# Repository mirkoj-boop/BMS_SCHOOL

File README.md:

# BMS  4S Li-Ion Battery Management System

> BMS PCB designed in KiCad for a 4S Li-Ion battery pack integrates cell protection, passive balancing, isolated AC/DC charging, and LED battery indication on a single board.

---

## Features

- **4S Li-Ion protection** via BQ77905 - OVP, UVP, OCD, SCD, OT/UT per cell
- **Passive cell balancing** (VC1–VC5)
- **Isolated flyback AC/DC charger** - VIPer26LD + PC817 + TL431 feedback
- **10-segment LED battery indicator** - LM3914
- **AC EMI filter** - X+Y capacitors, varistor surge protection
- **Temperature monitoring** - NTC thermistor on TS pin

---

## Specifications

| Parameter | Value |
|---|---|
| Cell configuration | 4S Li-Ion |
| Nominal pack voltage | 14.4 V |
| Full charge voltage | 16.8 V |
| Charge current | 2 A |
| Charger input |230V(50Hz) |
| Design tool | KiCad 10 |

---

## Key Components

| Reference | Part | Function |
|---|---|---|
| U21 | BQ77905 | BMS IC - protection + balancing |
| U18 | VIPer26LD | Flyback AC/DC controller |
| U3 | LM3914 | LED battery level indicator |
| U2 | PC817 | Optocoupler - galvanic isolation |
| U1 | TL431DBZ | Voltage reference - feedback |
| T3 | Würth EE20_10_6_750811647 | Flyback transformer |
| Q22, Q23 | CSD19531Q5A | N-ch MOSFETs - charge/discharge path |
| D2 | KBPC | AC bridge rectifier |
| FL2 | P300PL104M275xC332 | AC EMI filter |
| RV01 | Varistor | Surge/overvoltage protection |
| TH2 | Thermistor | Temperature sense (TS pin) |

---

## System Architecture

```
230V(50Hz) ──► FL2 (EMI filter) ──► D2 (rectifier) ──► U18 VIPer26LD
                                                              │
                                                         T3 transformer
                                                        ╱             ╲
                                               Aux winding         Secondary
                                                    │                   │
                                               VDD (~5V)           VO (16.8V)
                                                                        │
                                                              PC817 + TL431
                                                             (isolated feedback)

4S Pack (BT15–BT18) ──► BQ77905 ──► CSD19531Q5A MOSFETs ──► PACK+ / PACK-
                              │
                          LM3914 ──► LED bar
```

## References

- [TI SLUA793 — BQ77905 Design Considerations in High-Current Applications](https://www.ti.com/lit/an/slua793/slua793.pdf)
- [DigiKey Reference Design — AC/DC SMPS Multi-Output (STEVAL-ISA081V1)](https://www.digikey.com/reference-designs/en/ac-dc-and-dc-dc-conversion/ac-dc-smps-multi-output/752)
- [EEVblog — How Does This Flyback Feedback Circuit Work?](https://www.eevblog.com/forum/projects/how-does-this-flyback-feedback-circuit-work/)
- [BQ77905 Product Page — Texas Instruments](https://www.ti.com/product/BQ77905)
- [VIPer26LD Datasheet — STMicroelectronics](https://www.st.com/en/power-management/viper26ld.html)

---

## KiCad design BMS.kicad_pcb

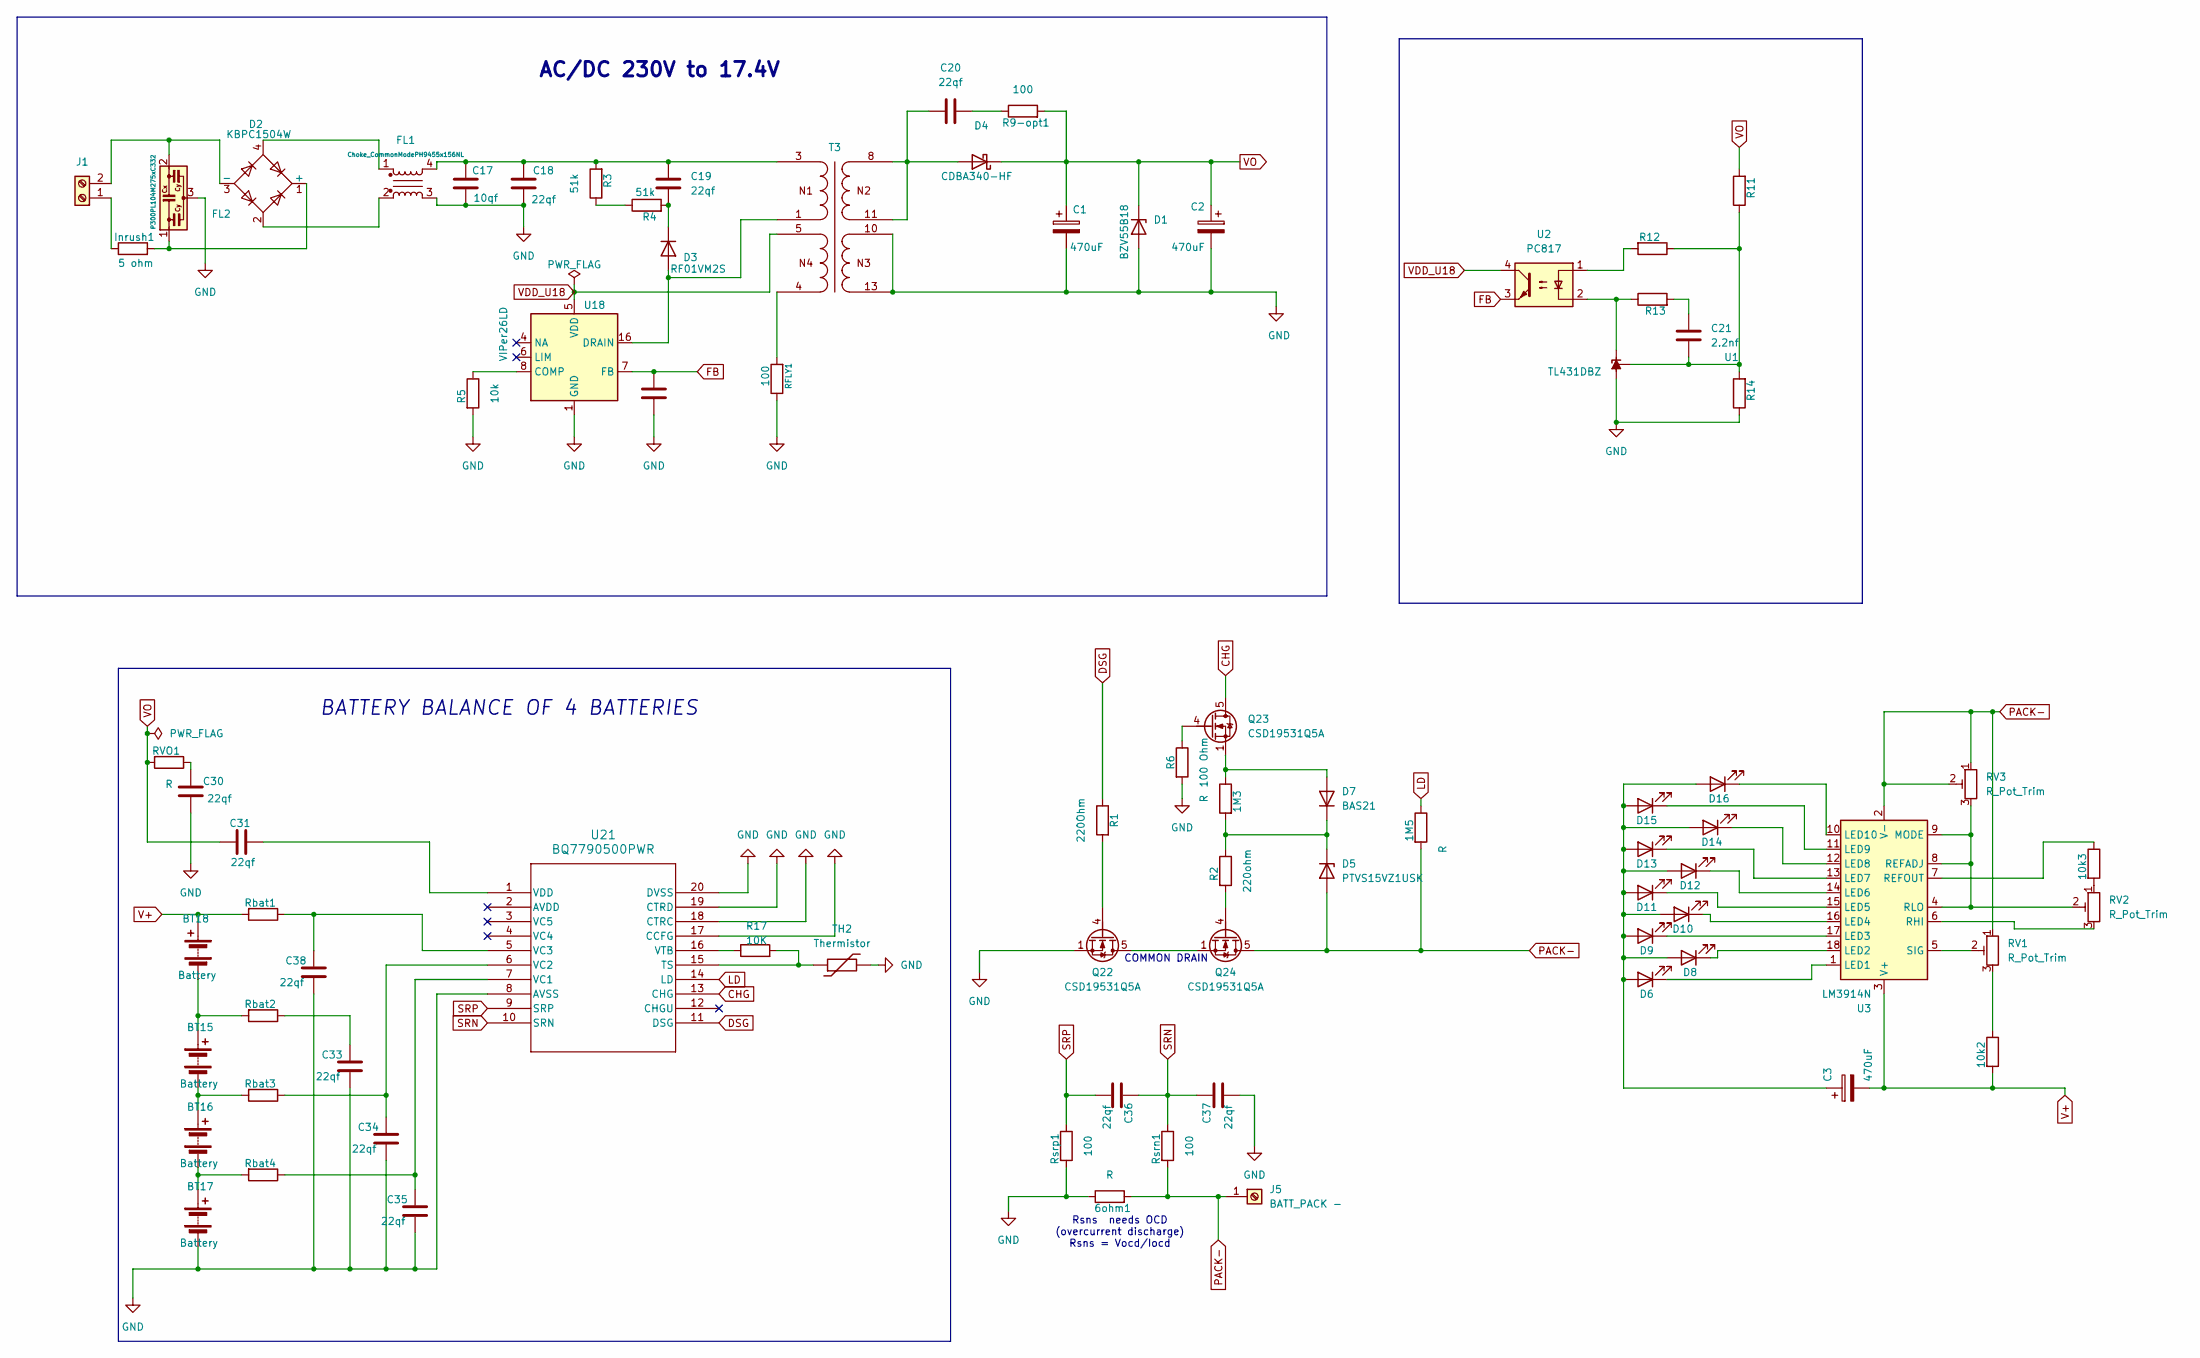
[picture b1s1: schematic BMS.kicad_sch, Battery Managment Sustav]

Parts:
1M3, 1M5, 6ohm1: R; R_0805_2012Metric
10k2, 10k3: 10k; R_0805_2012Metric
BT15, BT16, BT17, BT18: Battery; BatteryHolder_Keystone_2460_1xAA
C1, C2, C3: 470uF; C_0805_2012Metric
C17: 10qf; CP_Radial_D5.0mm_P2.00mm
C18, C19: 22qf; CP_Radial_D5.0mm_P2.00mm
C20: 22qf; C_0805_2012Metric
C21: 2.2nf; C_0805_2012Metric
C24: 4.7nF; CP_Radial_D5.0mm_P2.00mm
C30, C31, C33, C34, C35, C36, C37, C38: 22qf; C_0402_1005Metric
D1: BZV55B18; D_MiniMELF
D2: KBPC1504W; Diode_Bridge_GeneSiC_KBPC_W
D3: RF01VM2S; D_SOD-323
D4: CDBA340-HF; D_SMA
D5: PTVS15VZ1USK; Nexperia_DSN1608-2_1.6x0.8mm
D6, D8, D9, D10, D11, D12, D13, D14, D15, D16: LED; LED_0805_2012Metric
D7: BAS21; SOT-23
FL1: Choke_CommonModePH9455x156NL; L_CommonMode_PulseElectronics_PH9455xxx6NL_2
FL2: P300PL104M275xC332; Filter_KEMET_PZB300_24.0x12.5mm_P10.0mm
Inrush1: 5 ohm; R_Axial_DIN0204_L3.6mm_D1.6mm_P5.08mm_Horizontal
J1: Screw_Terminal_01x02; TerminalBlock_Phoenix_MKDS-1,5-2_1x02_P5.00mm_Horizontal
J5: BATT_PACK -; TerminalBlock_MetzConnect_360271_1x01_Horizontal_ScrewM3.0_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
Q22, Q23, Q24: CSD19531Q5A; TDSON-8-1
R1: 220Ohm; R_0805_2012Metric
R2: 220ohm; R_0805_2012Metric
R3, R4: 51k; R_0805_2012Metric
R5: 10k; R_0805_2012Metric
R6: 100 Ohm; R_0805_2012Metric
R9-opt1: 100; R_0805_2012Metric
R11, R12, R13, R14: R; R_0805_2012Metric
R17: 10K; R_0805_2012Metric
RFLY1: 100; R_0805_2012Metric
RV1: R_Pot_Trim; R_0805_2012Metric
RV2, RV3: R_Pot_Trim; Potentiometer_ACP_CA6-VSMD_Vertical
RVO1: R; R_0805_2012Metric
Rbat1, Rbat2, Rbat3, Rbat4: 1k; R_0805_2012Metric
Rsrn1: 100; R_0805_2012Metric
Rsrp1: 100; R_0805_2012Metric
T3: EE20_10_6_750811647; Transformer_Wuerth_760871131; Part Number 750811647
TH2: Thermistor; R_0805_2012Metric
U1: TL431DBZ; SOT-23
U2: PC817; DIP-4_W7.62mm
U3: LM3914N; DIP-18_W7.62mm
U18: VIPer26LD; SOIC-16_3.9x9.9mm_P1.27mm
U21: BQ7790500PWR; TSSOP-20_4.4x6.5mm_P0.65mm

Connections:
CHG: Q23.5 (D), U21.13 (CHG)
DSG: R1.1, U21.11 (DSG)
FB: C24.1, U2.3, U18.7 (FB)
GND: 6ohm1.1, BT17.2 (-), C1.2, C2.2, C17.2, C18.2, C24.2, C30.1, C33.1, C34.1, C35.1, C37.1, C38.1, D1.2 (A), FL1.3, FL2.3, Q22.1 (S), Q22.2 (S), Q22.3 (S), R5.2, R6.2, R14.1, RFLY1.1, Rsrp1.2, T3.10, T3.13, TH2.2, U1.3 (A), U18.1 (GND), U18.2 (GND), U21.8 (AVSS), U21.17 (CCFG), U21.18 (CTRC), U21.19 (CTRD), U21.20 (DVSS)
LD: 1M5.1, U21.14 (LD)
unnamed: 10k2.1, RV1.3
unnamed: 10k3.2, RV2.1
unnamed: BT15.1 (+), BT18.2 (-), Rbat2.2
unnamed: BT15.2 (-), BT16.1 (+), Rbat3.2
unnamed: BT16.2 (-), BT17.1 (+), Rbat4.2
unnamed: C17.1, C18.1, C19.1, FL1.4, R3.2, T3.3
unnamed: C20.1, R9-opt1.1
unnamed: C21.2, R13.2
unnamed: C30.2, RVO1.1
unnamed: C33.2, Rbat2.1
unnamed: D2.1 (+), FL2.1, Inrush1.2
unnamed: D2.3 (-), FL2.2, J1.2
unnamed: D2.2, FL1.2
unnamed: D2.4, FL1.1
unnamed: D3.2 (A), T3.1, U18.13 (DRAIN), U18.14 (DRAIN), U18.15 (DRAIN), U18.16 (DRAIN)
unnamed: C19.2, D3.1 (K), R4.2
unnamed: C20.2, D4.2 (A), T3.8, T3.11
unnamed: 1M3.2, D5.1 (K), D7.3 (K), R2.1
unnamed: D6.1 (K), U3.1 (LED1)
unnamed: 1M3.1, D7.1 (A), Q23.1 (S), Q23.2 (S), Q23.3 (S)
unnamed: D8.1 (K), U3.18 (LED2)
unnamed: D9.1 (K), U3.17 (LED3)
unnamed: C3.1, D6.2 (A), D8.2 (A), D9.2 (A), D10.2 (A), D11.2 (A), D12.2 (A), D13.2 (A), D14.2 (A), D15.2 (A), D16.2 (A)
unnamed: D10.1 (K), U3.16 (LED4)
unnamed: D11.1 (K), U3.15 (LED5)
unnamed: D12.1 (K), U3.14 (LED6)
unnamed: D13.1 (K), U3.13 (LED7)
unnamed: D14.1 (K), U3.12 (LED8)
unnamed: D15.1 (K), U3.11 (LED9)
unnamed: D16.1 (K), U3.10 (LED10)
unnamed: Inrush1.1, J1.1
unnamed: Q22.5 (D), Q24.1 (S), Q24.2 (S), Q24.3 (S)
unnamed: Q22.4 (G), R1.2
unnamed: Q23.4 (G), R6.1
unnamed: Q24.4 (G), R2.2
unnamed: R3.1, R4.1
unnamed: R12.2, U2.1
unnamed: RFLY1.2, T3.4
unnamed: R13.1, U1.1 (K), U2.2
unnamed: C21.1, R11.1, R12.1, R14.2, U1.2 (REF)
unnamed: RV2.2, RV3.3, U3.4 (RLO), U3.8 (REFADJ), U3.9 (MODE)
unnamed: 10k3.1, U3.7 (REFOUT)
unnamed: RV2.3, U3.6 (RHI)
unnamed: RV1.2, U3.5 (SIG)
unnamed: R5.1, U18.8 (COMP)
unnamed: R17.2, TH2.1, U21.15 (TS)
unnamed: C35.2, Rbat4.1, U21.7 (VC1)
unnamed: C34.2, Rbat3.1, U21.6 (VC2)
unnamed: C38.2, Rbat1.1, U21.5 (VC3)
unnamed: C31.2, U21.1 (VDD)
unnamed: R17.1, U21.16 (VTB)
PACK-: 1M5.2, 6ohm1.2, D5.2 (A), J5.1 (Pin_1_1), Q24.5 (D), RV1.1, RV3.1, RV3.2, Rsrn1.2, U3.2 (V-)
SRN: C36.2, C37.2, Rsrn1.1, U21.10 (SRN)
SRP: C36.1, Rsrp1.1, U21.9 (SRP)
V+: 10k2.2, BT18.1 (+), C3.2, Rbat1.2, U3.3 (V+)
VDD_U18: T3.5, U2.4, U18.5 (VDD)
VO: C1.1, C2.1, C31.1, D1.1 (K), D4.1 (K), R9-opt1.2, R11.2, RVO1.2

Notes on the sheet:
Rsns needs OCD (overcurrent discharge) Rsns = Vocd/Iocd
COMMON DRAIN
AC/DC 230V to 17.4V
BATTERY BALANCE OF 4 BATTERIES

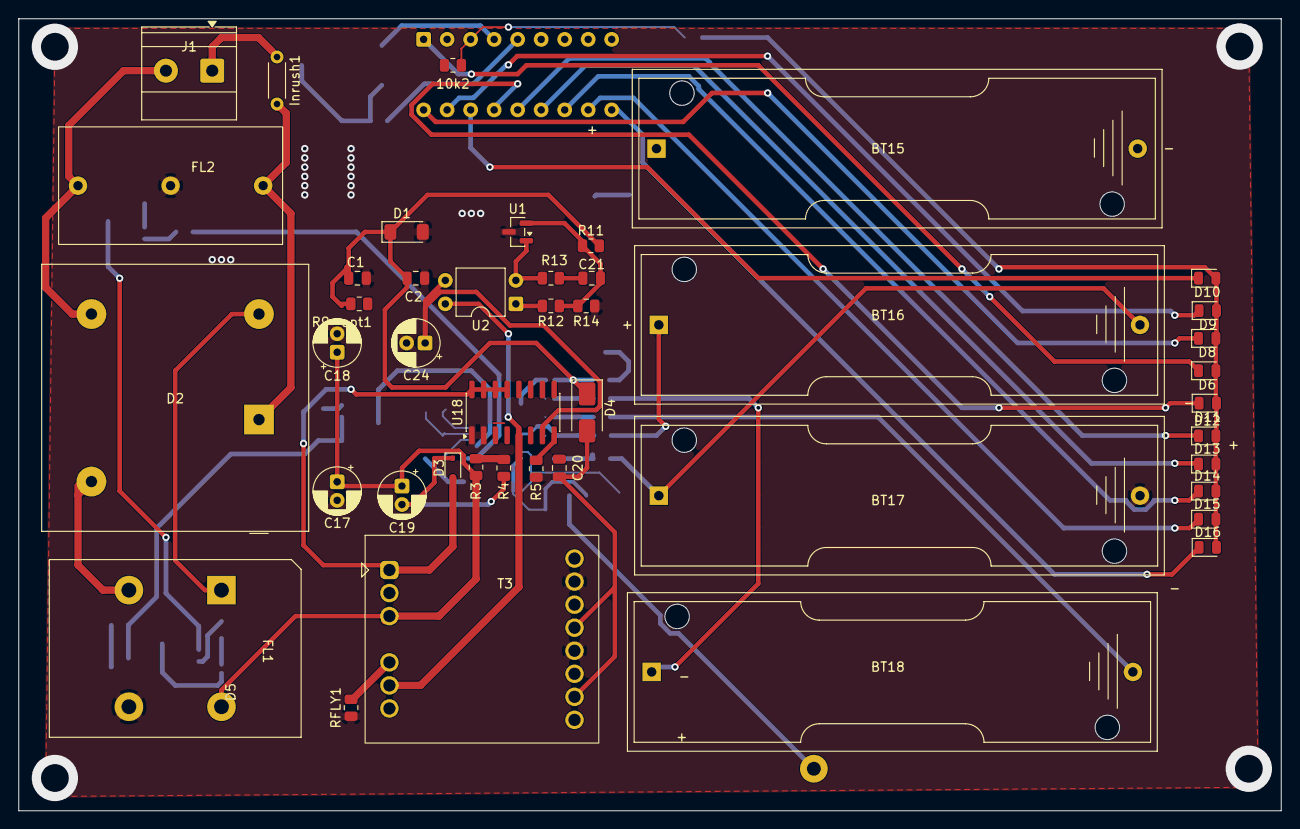
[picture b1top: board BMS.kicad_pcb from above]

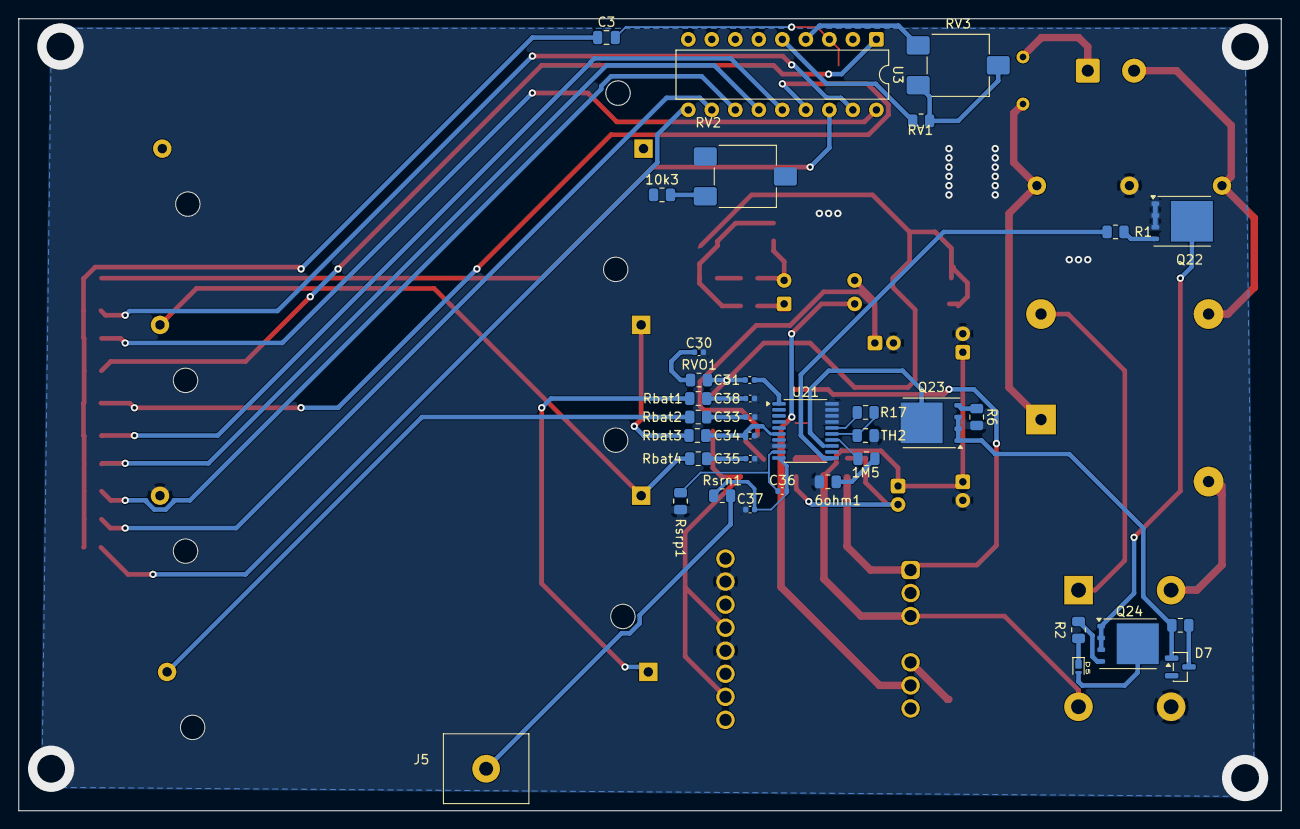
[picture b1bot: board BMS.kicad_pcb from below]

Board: 2 copper layers, 136.4 x 85.6 mm, 80 parts (36 on the bottom side), 61 nets.

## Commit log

2026-04-26 Lecture Update
    Updated some forms in charging section
2026-05-05 ac dc converter set with flyback transformer
    Preparation for 5V with 12V headers
2026-05-05 Case
    First case commit
2026-05-07 Chip decided
2026-05-07 Change header level for BQ77905 Design Consideration
2026-06-14 flyback transformer
    Flyback transformer fixed along with regulation
2026-06-15 Update
    updated Flyback control
2026-06-15 update schematic view
2026-06-15 Add BMS backup zip and image
    Add a BMS backup archive and a related image to the repository. Files added: BMS-backups/BMS-2026-06-15_230002.zip (backup archive) and images/bms.jpg (reference image for BMS).
2026-06-15 Update README with image and content changes
    Added an image to the README and updated the content.
2026-06-15 Rename image to include space before extension
    Rename images/bms.jpg to images/bms .jpg (100% similarity). No content changes—only the filename was changed to include a space before the .jpg extension. Update any references to the image to avoid 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
2026-06-15 Remove backup zips and KiCad lock files
    Delete legacy BMS backup archives and temporary KiCad lock files from the repository to clean up large binary backups and stale editor lock files. Removed files: BMS-backups/BMS-2026-06-14_190508.zip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
2026-06-16 Add AC/DC & balancer sheets; update BMS schematic
    Add new schematic files (acdc, acdcflyback, acdc.sch.kicad_sch, balancer/balance, overcharge, overcurrent) plus autosave copies, a backup zip and KiCad lock files. Update BMS.kicad_pro to register th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
2026-06-16 Add EMI filter symbol; adjust schematic labels/wiring
    Add two backup ZIPs and update KiCad project/schematic. BMS.kicad_pro: add ngspice config, simplify used_designators and trim sheets list. BMS.kicad_sch: add a new EMI filter symbol (P300PL104M275xC3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
2026-06-19 Add Wurth connector 3D model & footprint
    Add STEP 3D model and footprint for T_Wurth_WE-OLTI-EE20_10_6_750811647 and update KiCad project files. BMS.kicad_pro and BMS.kicad_sch were modified, autosave schematic files removed, and backup ZIP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
2026-06-21 Add full KiCad PCB file and backups
    Replace the placeholder BMS.kicad_pcb with the complete KiCad PCB data (version 20260206) including layers, setup, footprints, pads and 3D models. Update related project files (BMS.kicad_prl, BMS.kic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
2026-06-21 Battery level indicator LM3914
2026-06-22 Update PCB stackup, footprints, and add backups
    Add multiple BMS backup archives and project PNG; modify BMS.kicad_pcb with an explicit stackup (layers, thicknesses, dielectric), enable zone_defaults, and update many footprints and component defin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
2026-06-23 routing
2026-06-23 Update of routing
2026-06-24 Updated GND via and holes
    GND was missdirected at VO point and had to be fixed
2026-06-24 Routing update
2026-06-24 front layer route
2026-06-25 Routing update
    19 errors to go
2026-06-26 Add README for 4S Li-Ion Battery Management System
    Added detailed documentation for the 4S Li-Ion Battery Management System, including features, specifications, key components, system architecture, and references.
2026-06-26 Remove project status and author information
    Removed project status and author sections from README.
2026-06-26 Revise charger input and remove outdated sections
    Updated charger input specification and system architecture diagram. Removed sections on net references, current sensing, output voltage setting, and PCB notes.
2026-06-26 Fix formatting in README for features and components
    Updated formatting for consistency in README.
2026-06-26 Refine BMS description in README
    Removed 'Custom' from the description for clarity.
